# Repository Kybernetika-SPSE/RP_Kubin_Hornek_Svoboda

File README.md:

Model průmyslového šestiosého robota

Baví nás průmyslové technologie a robotika. Chceme sestavit model průmyslového kolaborativního robota, udělat k němu pendant a provést oživení.
Příští rok bychom toto rádi rozvinuli i do maturitní práce. Očekáváme, že získáme více praxe a více porozumění v tomto oboru a do budoucna nám budou velmi přínosné, ať už v práci, nebo na vysoké škole.
A hlavně... jsme borci

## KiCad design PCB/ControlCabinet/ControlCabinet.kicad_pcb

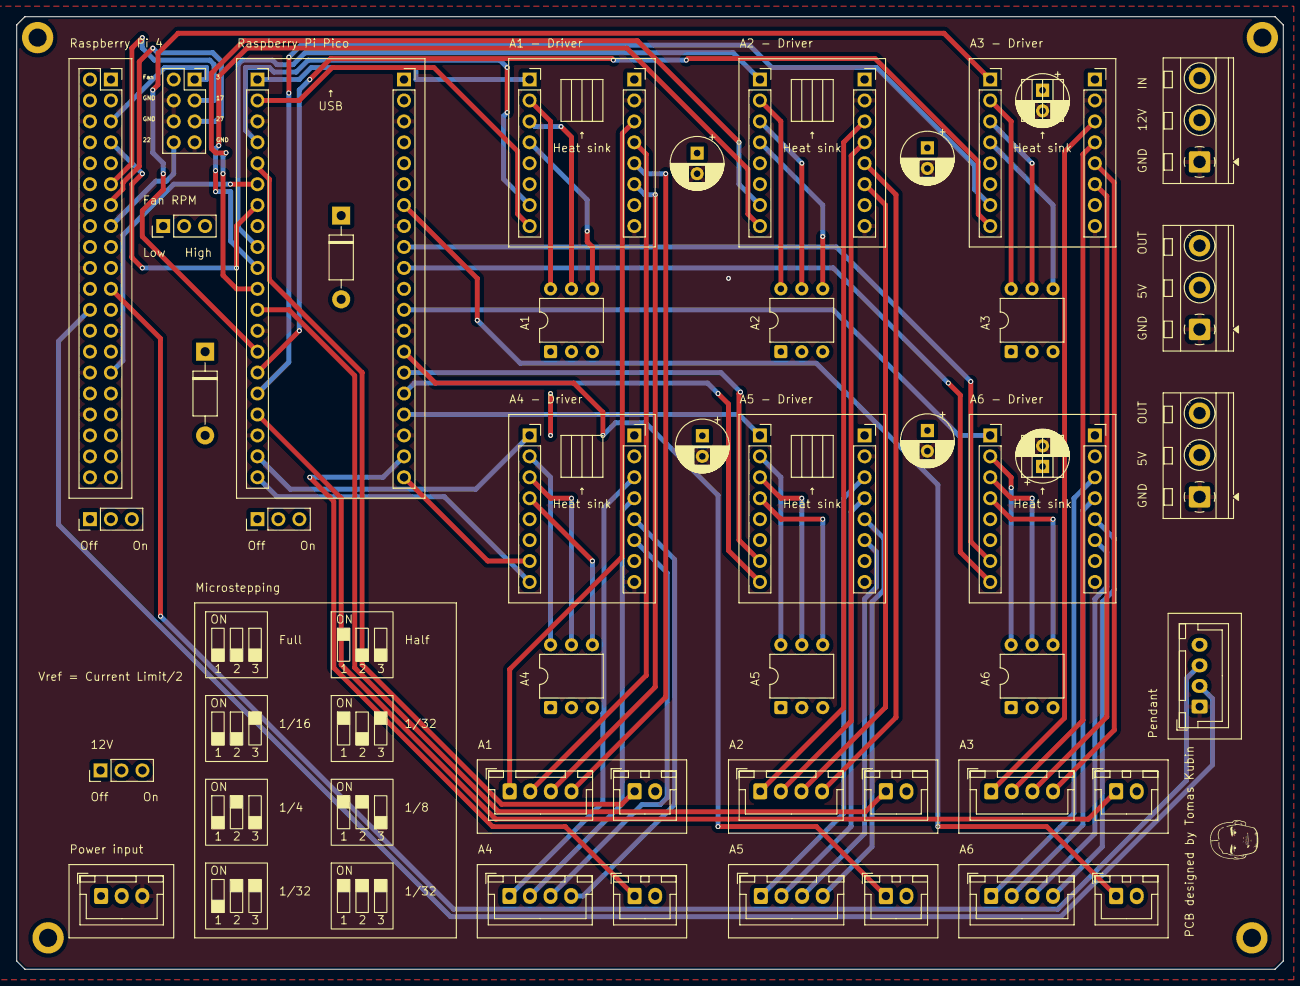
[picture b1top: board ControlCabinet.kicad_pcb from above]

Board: 4 copper layers, 153.7 x 115.6 mm, 51 parts (0 on the bottom side), 86 nets.

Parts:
C3, C4, C5, C6, C7, C8: 100uf; CP_Radial_D6.3mm_P2.50mm
D1, D2: 1N5817; D_DO-41_SOD81_P10.16mm_Horizontal
GPIO17: Conn_02x04_Odd_Even; PinSocket_2x04_P2.54mm_Vertical
J1, J2, J28: Screw_Terminal_01x03; TerminalBlock__1x03_P5.08mm_Horizontal
J3, J4, J6, J7, J8, J9, J10, J11, J12, J13, J14, J15: Conn_01x08; PinSocket_1x08_P2.54mm_Vertical
J5: Conn_01x03; JST_XH_B3B-XH-A_1x03_P2.50mm_Vertical
J16, J18, J20, J22, J24, J26, J30: Conn_01x04; JST_XH_B4B-XH-A_1x04_P2.50mm_Vertical
J17, J19, J21, J23, J25, J27: Conn_01x02; JST_XH_B2B-XH-A_1x02_P2.50mm_Vertical
Pi4: Conn_02x20_Odd_Even; PinSocket_2x20_P2.54mm_Vertical
PicoL1: Conn_01x20; PinSocket_1x20_P2.54mm_Vertical
PicoR1: Conn_01x20; PinSocket_1x20_P2.54mm_Vertical
SW1, SW2, SW3, SW4, SW5, SW6: SW_DIP_x03; DIP-6_W7.62mm
SW7, SW10: SW_SPDT; Slide_Switch_1x03_P2.54mm
SW8, SW9: Slide_Switch; Slide_Switch_1x03_P2.54mm

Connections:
3V3_Pi4: Pi4.2, Pi4.18, SW10.2 (C)
+3V3: J3.5, J3.6, J6.5, J6.6, J8.5, J8.6, J10.5, J10.6, J12.5, J12.6, J14.5, J14.6, J17.2, J19.2, J21.2, J23.2, J25.2, J27.2, PicoR1.5, SW1.1, SW1.2, SW1.3, SW2.1, SW2.2, SW2.3, SW3.1, SW3.2, SW3.3, SW4.1, SW4.2, SW4.3, SW5.1, SW5.2, SW5.3, SW6.1, SW6.2, SW6.3
+5V: J1.2, J5.1, J28.2, J30.4, SW7.3 (A), SW8.3 (A)
+12V: C3.1, C4.1, C5.1, C6.1, C7.1, C8.1, J2.2, J4.1, J7.1, J9.1, J11.1, J13.1, J15.1, SW9.1 (B)
/A1.A1: J4.5, J16.4
/A1.A2: J4.6, J16.3
/A1.B1: J4.4, J16.2
/A1.B2: J4.3, J16.1
/A1.M0: J3.2, SW1.6
/A1.M1: J3.3, SW1.5
/A1.M2: J3.4, SW1.4
/A1_DIR: J3.8, PicoL1.2
/A1_EN: J3.1, PicoL1.1
/A1_HOME: J17.1, PicoL1.5
/A1_STEP: J3.7, PicoL1.4
/A2.A1: J7.5, J18.4
/A2.A2: J7.6, J18.3
/A2.B1: J7.4, J18.2
/A2.B2: J7.3, J18.1
/A2.M0: J6.2, SW2.6
/A2.M1: J6.3, SW2.5
/A2.M2: J6.4, SW2.4
/A2_DIR: J6.8, PicoL1.10
/A2_EN: J6.1, PicoL1.9
/A2_HOME: J19.1, PicoL1.12
/A2_STEP: J6.7, PicoL1.11
/A3.A1: J9.5, J20.4
/A3.A2: J9.6, J20.3
/A3.B1: J9.4, J20.2
/A3.B2: J9.3, J20.1
/A3.M0: J8.2, SW3.6
/A3.M1: J8.3, SW3.5
/A3.M2: J8.4, SW3.4
/A3_DIR: J8.8, PicoL1.15
/A3_EN: J8.1, PicoL1.14
/A3_HOME: J21.1, PicoL1.17
/A3_STEP: J8.7, PicoL1.16
/A4.A1: J11.5, J22.4
/A4.A2: J11.6, J22.3
/A4.B1: J11.4, J22.2
/A4.B2: J11.3, J22.1
/A4.M0: J10.2, SW4.6
/A4.M1: J10.3, SW4.5
/A4.M2: J10.4, SW4.4
/A4_DIR: J10.8, PicoL1.20
/A4_EN: J10.1, PicoL1.19
/A4_HOME: J23.1, PicoR1.19
/A4_STEP: J10.7, PicoR1.20
/A5.A1: J13.5, J24.4
/A5.A2: J13.6, J24.3
/A5.B1: J13.4, J24.2
/A5.B2: J13.3, J24.1
/A5.M0: J12.2, SW5.6
/A5.M1: J12.3, SW5.5
/A5.M2: J12.4, SW5.4
/A5_DIR: J12.8, PicoR1.16
/A5_EN: J12.1, PicoR1.17
/A5_HOME: J25.1, PicoR1.14
/A5_STEP: J12.7, PicoR1.15
/A6.A1: J15.5, J26.4
/A6.A2: J15.6, J26.3
/A6.B1: J15.4, J26.2
/A6.B2: J15.3, J26.1
/A6.M0: J14.2, SW6.6
/A6.M1: J14.3, SW6.5
/A6.M2: J14.4, SW6.4
/A6_DIR: J14.8, PicoR1.10
/A6_EN: J14.1, PicoR1.12
/A6_HOME: J27.1, PicoR1.7
/A6_STEP: J14.7, PicoR1.9
/DOOR: J1.3, J2.3, J28.3
/GPIO3: GPIO17.1, Pi4.6
/GPIO17: GPIO17.3, Pi4.12
/GPIO22: GPIO17.8, Pi4.16
/GPIO27: GPIO17.5, Pi4.14
/PendantRX_PiTX: J30.2, Pi4.23
/PendantTX_PiRX: J30.3, Pi4.22
/PicoRX_PiTX: Pi4.8, PicoL1.7
/PicoTX_PiRX: Pi4.30, PicoL1.6
/VSYS_Pi4: D2.1 (K), Pi4.1, Pi4.3, SW10.3 (A)
GND: C3.2, C4.2, C5.2, C6.2, C7.2, C8.2, GPIO17.4, GPIO17.6, GPIO17.7, J1.1, J2.1, J4.2, J4.8, J5.3, J7.2, J7.8, J9.2, J9.8, J11.2, J11.8, J13.2, J13.8, J15.2, J15.8, J28.1, J30.1, Pi4.5, Pi4.10, Pi4.13, Pi4.19, Pi4.26, Pi4.29, Pi4.33, PicoL1.3, PicoL1.8, PicoL1.13, PicoL1.18, PicoR1.3, PicoR1.8, PicoR1.13, PicoR1.18
unnamed: D1.2 (A), SW7.1 (B)
unnamed: D2.2 (A), SW8.1 (B)
unnamed: GPIO17.2, SW10.1 (B)
unnamed: J5.2, SW9.3 (A)
VSYS: D1.1 (K), PicoR1.2

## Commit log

2024-11-26 Upload zadání
2024-11-26 Create PENDANT
2024-12-03 Create testovaciSoubor
2024-12-03 Update testovaciSoubor
2024-12-03 zmena PENDANTU
2024-12-06 testik
2024-12-19 Organizace
2024-12-19 progres
2025-01-17 Reorganizace souborů
2025-01-18 Initial upload
    Hoodně alpha verze (jen zatím)
2025-01-20 Optimalizace a pŕidání nových funkcí
    Drobná optimalizace kódu. Přidání homování a limitů natočení pro každou z os
2025-01-22 Bugfixes
    Opravena docela podstatná chyba, teď již v pořádku
2025-01-22 Rozšíření funkcí
    Příprava pro komunikaci s druhým raspberry, zatím přes tcp, než se mi povede vyřešit převodník napětí pro I2C. Kód ještě potřebuje optimalizaci.
2025-01-23 Initial upload
    Sice zatím skoro žádný kód, ale je funkční, z toho mám radost, protože to trvalo
2025-01-23 Zprovoznění komunikace
    Hlavní chyba nebyla tady, ale na serveru
2025-01-23 Nahrání mého progress reportu a opravení názvu složky
2025-01-24 Progress Report Leden
2025-01-24 Nahrazení špatné verze dokumentace
2025-01-24 Optimalizace
2025-03-02 Progress report
2025-03-18 ControlHead -> ControlCabinet
    Přejmenování + skoro finální verze
2025-03-18 Nové verze kódů pro obě Raspberry
2025-03-20 Postup za Únor
2025-04-01 Progress report Brezen + zavisle soubory
2025-04-14 vylepšení kódu
2025-04-15 Create Model
2025-04-20 PR_Březen
2025-04-22 Komunikace mezi Pi4 a pendantem
2025-04-29 Create Dokumentace
2025-04-29 Oprava RP za březen
2025-04-30 Gitlab dokumentace
2025-04-30 Odevzdani dokumentace
2025-04-30 Oprava příloh
